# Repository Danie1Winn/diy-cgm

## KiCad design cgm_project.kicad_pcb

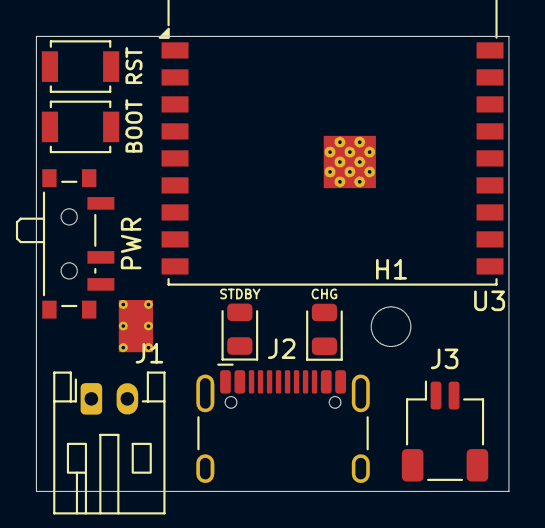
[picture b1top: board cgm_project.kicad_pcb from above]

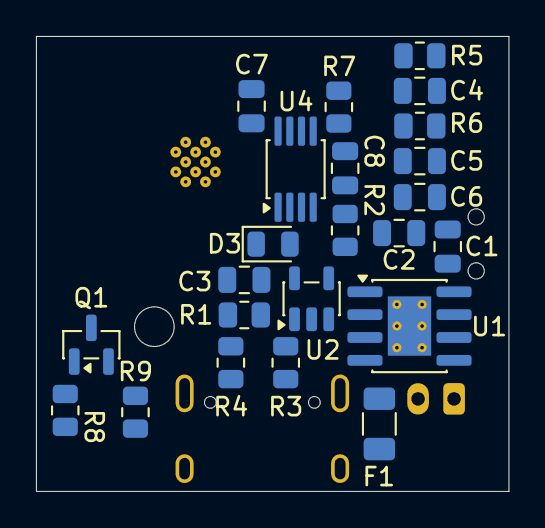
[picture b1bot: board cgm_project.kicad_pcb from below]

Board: 2 copper layers, 26.2 x 25.3 mm, 33 parts (23 on the bottom side), 22 nets, no tracks yet.

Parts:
BOOT: BOOT; SW_SPST_B3U-1000P
C1, C2, C3, C5: 10uF; C_0805_2012Metric
C4: 1uF; C_0805_2012Metric
C6, C7: 0.1uF; C_0805_2012Metric
C8: 330pF; C_0805_2012Metric
CHG: RED LED; LED_0805_2012Metric
D3: VEMD5010X01; LED_0805_2012Metric
F1: 500mA PTC Fuse; Fuse_1206_3216Metric
H1: MountingHole; MountingHole_2.2mm_M2
J1: JST BATT CONNECTOR; JST_PH_S2B-PH-K_1x02_P2.00mm_Horizontal
J2: USB_C_Receptacle_USB2.0_16P; USB_C_Receptacle_HCTL_HC-TYPE-C-16P-01A
J3: Conn_01x02_MountingPin; JST_SH_SM02B-SRSS-TB_1x02-1MP_P1.00mm_Horizontal
PWR: SW_SPDT; SW_SPDT_PCM12
Q1: AO3400; SOT-23
R1: 2k; R_0805_2012Metric
R2: 1k; R_0805_2012Metric
R3, R4: 5.1k; R_0805_2012Metric
R5, R6, R8: 10k; R_0805_2012Metric
R7: 4.7M; R_0805_2012Metric
R9: 33; R_0805_2012Metric
RST: RESET; SW_SPST_B3U-1000P
STDBY: GREEN LED; LED_0805_2012Metric
U1: TP4056-42-ESOP8; SOIC-8-1EP_3.9x4.9mm_P1.27mm_EP2.41x3.3mm_ThermalVias
U2: AP2112K-3.3; SOT-23-5
U3: ESP32-C3-WROOM-02
U4: OPA380; MSOP-8_3x3mm_P0.65mm

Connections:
+3V3: C3.1, C5.1, C6.2, C7.2, R5.1, R6.1, R9.1, U2.5 (VOUT), U3.1 (3V3), U4.7 (V+)
/AFE_ADC_IN: C8.1, R7.1, U3.18 (IO0), U4.6
/IR_LED_PWM: Q1.1 (G), R8.1, U3.16 (IO2)
/USB_D+: J2.A6 (D+), J2.B6 (D+), U3.14 (IO19)
/USB_D-: J2.A7 (D-), J2.B7 (D-), U3.13 (IO18)
/VBAT: C2.1, J1.1, PWR.1 (A), U1.5 (BAT)
/VBUS_5V: F1.2, R1.1, U1.4 (V_{CC})
GND: BOOT.2, C1.1, C2.2, C3.2, C4.2, C5.2, C6.1, C7.1, D3.1 (K), J1.2, J2.A1 (GND), J2.A12 (GND), J2.B1 (GND), J2.B12 (GND), J2.SH (SHIELD), J3.MP (MountPin), Q1.2 (S), R2.2, R3.2, R4.2, R8.2, RST.1, U1.1 (TEMP), U1.3 (GND), U2.2 (GND), U3.9 (GND), U3.19 (GND), U4.3 (+), U4.4 (V-)
unnamed: CHG.2 (A), R1.2, STDBY.2 (A)
unnamed: STDBY.1 (K), U1.6 (~STDBY)
unnamed: CHG.1 (K), U1.7 (~CHRG)
unnamed: C8.2, D3.2 (A), R7.2, U4.2 (-)
unnamed: F1.1, J2.A4 (VBUS), J2.A9 (VBUS), J2.B4 (VBUS), J2.B9 (VBUS)
unnamed: J2.A5 (CC1), R3.1
unnamed: J2.B5 (CC2), R4.1
unnamed: J3.1, R9.2
unnamed: J3.2, Q1.3 (D)
unnamed: PWR.2 (B), U2.1 (VIN), U2.3 (EN)
unnamed: C1.2, U1.8 (CE)
unnamed: R2.1, U1.2 (PROG)
unnamed: C4.1, R6.2, RST.2, U3.2 (EN)
unnamed: BOOT.1, R5.2, U3.8 (IO9)

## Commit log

2026-05-19 chore: initial repo setup
2026-05-20 feat: complete power management block with tp4056 and ap2112k
2026-05-20 feat: implement fused native USB-C receptacle block
2026-05-20 feat: implement esp32-c3 core with boot logic and net labels
2026-05-20 feat: implement OPA380 transimpedance amplifier and photodiode array
2026-05-20 feat: implement N-channel MOSFET emitter driver block
2026-05-20 fix: resolve ERC power flag collisions, clear unused pin warning
2026-05-20 chore: assign physical footprint for all schematic component
2026-05-21 feat: replace onboard IR LED with off-board wire connector
2026-05-21 fix: resolve footprint pin mismatches for OPA380 and JST - Replace generic AFE opamp symbolw ith standard 8-pin alias, matching MSOP-8 package - Update wire harness connector to include mechanical pa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
2026-05-21 feat: placed MCU and USB-C interface components on PCB
2026-05-21 chore: finalize component placement for power management, USB interface
2026-05-21 chore: finalize ESP32-C3 MCU layout, boot logic, and decoupling
2026-05-21 chore: finalize placement for analog sensor array
2026-05-21 chore: finalize placement for emitter connector, current switch, limiter, and gate pulldown
2026-05-22 chore: switched to a double sided design - changed BOOT and RST to a more compact footpritn - moved all connectors and switches to front of board
2026-05-22 chore: placement of photodiode sensor array on bottom of PCB
2026-05-22 chore: placement of decoupling resistors and capacitors on bottom of PCB
2026-05-22 chore: placement of charger, LDO, fuse, and passives on back of PCB
2026-05-29 chore: finalize double-sided PCB floorplan - lock footprint positions for routing - position D3 for optimal finger placement - stack U4 analog island directly beaneath U3 to minimize noise on analog 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
2026-05-29 chore: add M2 mounting hole
